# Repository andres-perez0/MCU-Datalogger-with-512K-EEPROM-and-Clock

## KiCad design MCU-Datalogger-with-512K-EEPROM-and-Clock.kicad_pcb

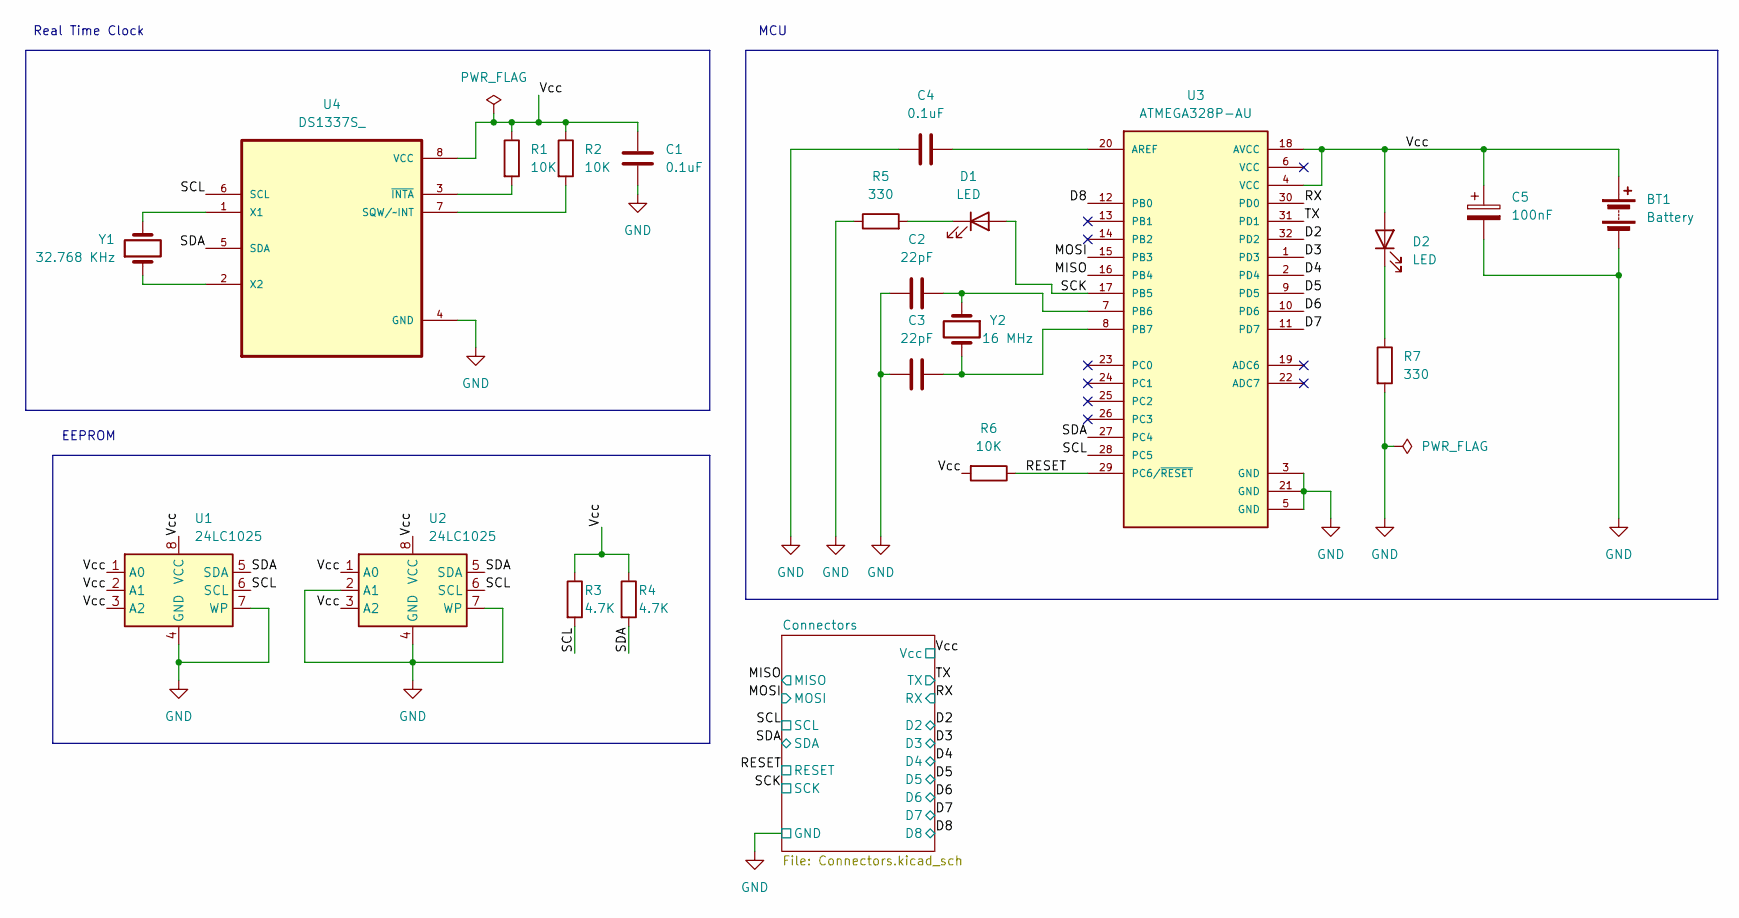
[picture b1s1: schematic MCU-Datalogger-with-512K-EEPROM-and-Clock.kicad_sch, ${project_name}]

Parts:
BT1: Battery; PinHeader_1x02_P2.54mm_Vertical
C1, C4: 0.1uF; C_0805_2012Metric
C2, C3: 22pF; C_0805_2012Metric
C5: 100nF; C_0805_2012Metric
D1, D2: LED; LED_0805_2012Metric
R1, R2, R6: 10K; R_0805_2012Metric
R3, R4: 4.7K; R_0805_2012Metric
R5, R7: 330; R_0805_2012Metric
U1, U2: 24LC1025; SOIC-8_5.3x5.3mm_P1.27mm
U3: ATMEGA328P-AU; QFP80P900X900X120-32N; PARTREV 8271A
U4: DS1337S_; SOIC127P600X175-8N
Y1: 32.768 KHz; Crystal_SMD_5032-2Pin_5.0x3.2mm_HandSoldering
Y2: 16 MHz; Crystal_SMD_5032-2Pin_5.0x3.2mm_HandSoldering

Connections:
/D2: U3.32 (PD2); also elsewhere on the board
/D3: U3.1 (PD3); also elsewhere on the board
/D4: U3.2 (PD4); also elsewhere on the board
/D5: U3.9 (PD5); also elsewhere on the board
/D6: U3.10 (PD6); also elsewhere on the board
/D7: U3.11 (PD7); also elsewhere on the board
/D8: U3.12 (PB0); also elsewhere on the board
/MISO: U3.16 (PB4); also elsewhere on the board
/MOSI: U3.15 (PB3); also elsewhere on the board
/RESET: R6.1, U3.29 (PC6/~RESET); also elsewhere on the board
/RX: U3.30 (PD0); also elsewhere on the board
/SCK: D1.2 (A), U3.17 (PB5); also elsewhere on the board
/SCL: R3.2, U1.6 (SCL), U2.6 (SCL), U3.28 (PC5), U4.6 (SCL); also elsewhere on the board
/SDA: R4.2, U1.5 (SDA), U2.5 (SDA), U3.27 (PC4), U4.5 (SDA); also elsewhere on the board
/TX: U3.31 (PD1); also elsewhere on the board
/Vcc: BT1.1 (+), C1.1, C5.1, D2.2 (A), R1.1, R2.1, R3.1, R4.1, R6.2, U1.1 (A0), U1.2 (A1), U1.3 (A2), U1.8 (VCC), U2.1 (A0), U2.3 (A2), U2.8 (VCC), U3.4 (VCC), U3.18 (AVCC), U4.8 (VCC); also elsewhere on the board
GND: BT1.2 (-), C1.2, C2.1, C3.2, C4.2, C5.2, R5.1, R7.2, U1.4 (GND), U1.7 (WP), U2.2 (A1), U2.4 (GND), U2.7 (WP), U3.3 (GND), U3.5 (GND), U3.21 (GND), U4.4 (GND); also elsewhere on the board
unnamed: D1.1 (K), R5.2
unnamed: D2.1 (K), R7.1
unnamed: C4.1, U3.20 (AREF)
unnamed: C2.2, U3.7 (PB6), Y2.1
unnamed: C3.1, U3.8 (PB7), Y2.2
unnamed: R2.2, U4.7 (SQW/~INT)
unnamed: U4.1 (X1), Y1.2
unnamed: U4.2 (X2), Y1.1
unnamed: R1.2, U4.3 (~INTA)

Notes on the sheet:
MCU
EEPROM
Real Time Clock

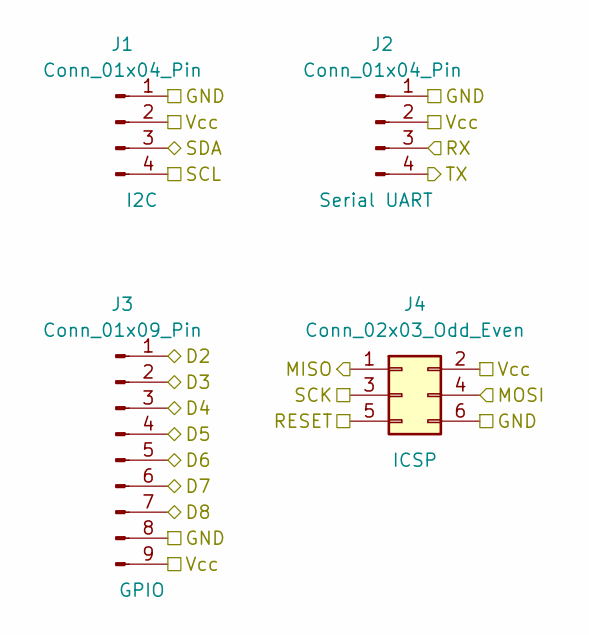
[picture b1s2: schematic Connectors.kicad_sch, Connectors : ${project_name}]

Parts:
J1, J2: Conn_01x04_Pin; PinHeader_1x04_P2.54mm_Vertical
J3: Conn_01x09_Pin; PinHeader_1x09_P2.54mm_Vertical
J4: Conn_02x03_Odd_Even; PinHeader_2x03_P2.54mm_Vertical

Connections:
/D2: J3.1; also elsewhere on the board
/D3: J3.2; also elsewhere on the board
/D4: J3.3; also elsewhere on the board
/D5: J3.4; also elsewhere on the board
/D6: J3.5; also elsewhere on the board
/D7: J3.6; also elsewhere on the board
/D8: J3.7; also elsewhere on the board
/MISO: J4.1; also elsewhere on the board
/MOSI: J4.4; also elsewhere on the board
/RESET: J4.5; also elsewhere on the board
/RX: J2.3; also elsewhere on the board
/SCK: J4.3; also elsewhere on the board
/SCL: J1.4; also elsewhere on the board
/SDA: J1.3; also elsewhere on the board
/TX: J2.4; also elsewhere on the board
/Vcc: J1.2, J2.2, J3.9, J4.2; also elsewhere on the board
GND: J1.1, J2.1, J3.8, J4.6; also elsewhere on the board

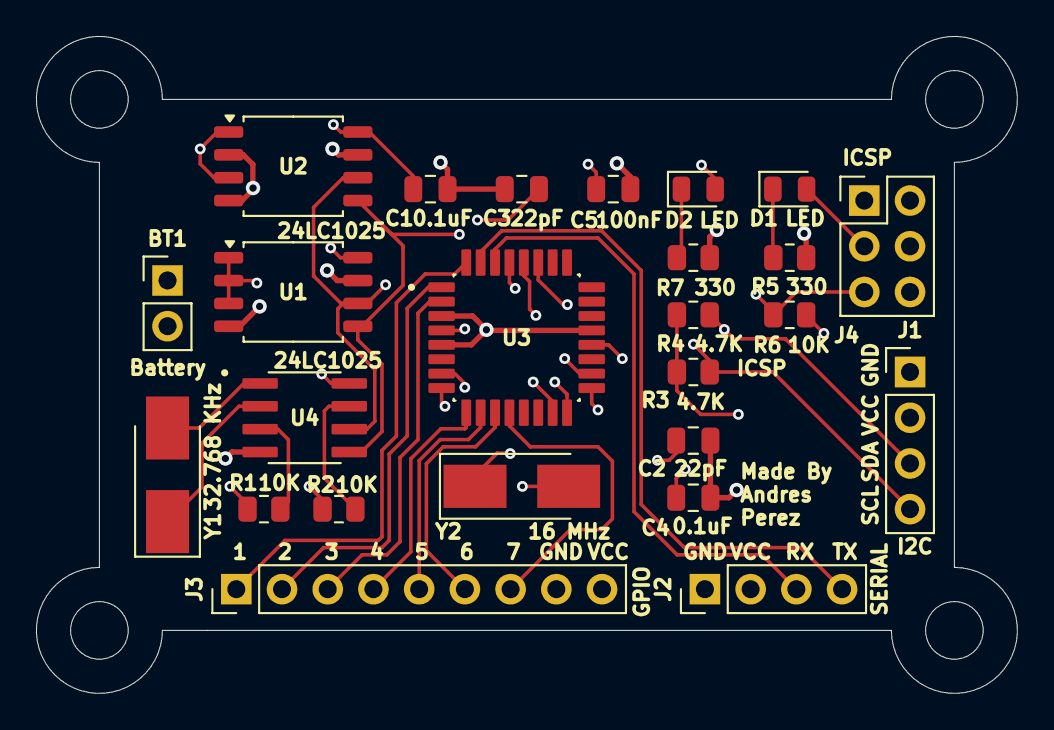
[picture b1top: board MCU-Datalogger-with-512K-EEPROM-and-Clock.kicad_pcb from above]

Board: 4 copper layers, 54.5 x 36.5 mm, 25 parts (0 on the bottom side), 26 nets.

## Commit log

2025-07-05 uploading kicad project files through powershell
2025-07-05 updated git ignore
2025-07-05 removed temporary files
2025-07-06 finalized schematic
2025-07-06 upaded gitignore and removed cached fp-lib-table
2025-07-06 uploaded page setting; restarting the board design
2025-07-06 remove the current board
2025-07-06 components added; now creating the branches
2025-07-06 pcb components layed out; requires routing
2025-07-06 2 layer board completed; minus annotation and further design rule checking
2025-07-06 2layer board completed with DRC completed[only small text constraint left]
2025-07-07 added git attributes file x2
2025-07-07 fixed schematic sck vs scl nets
2025-07-07 re-routed SCK and SCL board from new schematic
2025-07-07 did not included an kicad_prl file
2025-07-07 4layer board completed
